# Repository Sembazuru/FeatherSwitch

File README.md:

# FeatherSwitch
AdaFruit Feather Enable Switch Board. Designed in <a href="http://kicad-pcb.org/">KiCAD.</a>

This board connects the GND pin and the EN pin (opposite sides of the Feather boards) together with a switch,
ideally across the underside of the Feather board. The switch is next to the battery connector.
It doesn't obscure the battery connector, but does make it more difficult to remove the battery.
This can be ameliorated by mounting this board to either a Feather Wing, or the Feather Doubler (or Tripler)
This allows conveniently turning off the board without disconnecting either a battery or the USB cable.
This first version of the board has hole size and spacing for AdaFruit#<a href="https://www.adafruit.com/product/805">805</a> slide switch or mechanical equivalent.
Note: The holes are slightly too small for 0.25"sq header pins.

The design works best if the 2oz copper option is selected to get 0.8mm (1/32", or half standard) thick boards. These boards are available to order using the button below.</br>
<a href="https://oshpark.com/shared_projects/68Dy2ual"></img></a>

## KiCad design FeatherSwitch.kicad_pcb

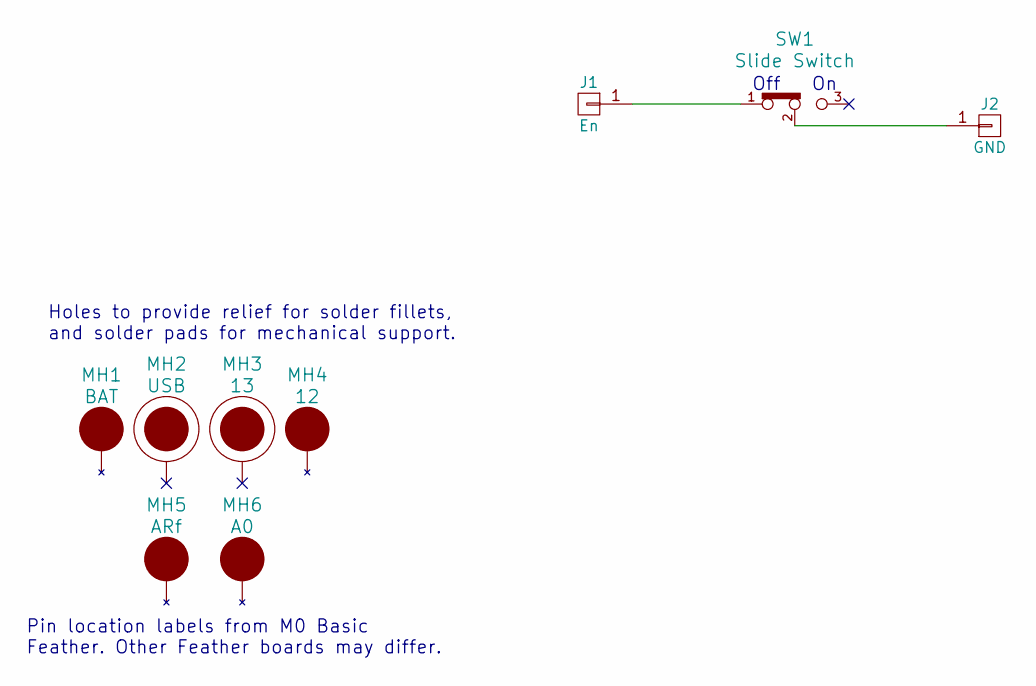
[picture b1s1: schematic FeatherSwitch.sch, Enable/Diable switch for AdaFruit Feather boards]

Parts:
J1: En; PAD_AdaFruit_Feather
J2: GND; PAD_AdaFruit_Feather
MH1: BAT; PAD-Clear_AdaFruit_Feather
MH2: USB; PAD_AdaFruit_Feather
MH3: 13; PAD_AdaFruit_Feather
MH4: 12; PAD-Clear_AdaFruit_Feather
MH5: ARf; PAD-Clear_AdaFruit_Feather
MH6: A0; PAD-Clear_AdaFruit_Feather
SW1: Slide Switch; SW_ADAFRUIT_508

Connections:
unnamed: J1.1, SW1.1 (Pole1)
unnamed: J2.1, SW1.2 (Throw)

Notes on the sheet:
Off
Pin location labels from M0 Basic Feather. Other Feather boards may differ.
Holes to provide relief for solder fillets, and solder pads for mechanical support.

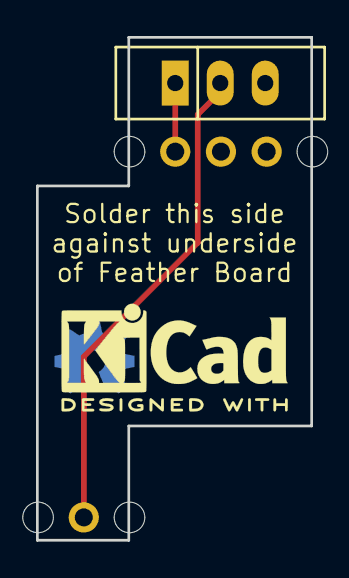
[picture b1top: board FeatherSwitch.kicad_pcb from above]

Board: 2 copper layers, 15.2 x 27.9 mm, 9 parts (0 on the bottom side), 2 nets.

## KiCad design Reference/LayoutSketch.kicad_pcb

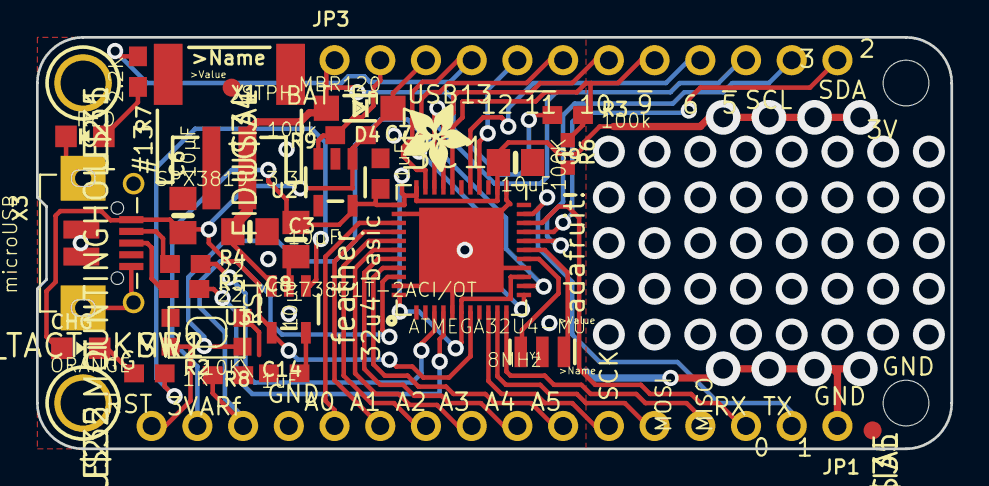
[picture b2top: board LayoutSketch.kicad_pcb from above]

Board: 2 copper layers, 50.8 x 22.9 mm, 36 parts (0 on the bottom side), 37 nets.

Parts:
@HOLE0, @HOLE1: (no value)
C3, C6, C8: 10µF; 0805-NO
C7, C14: 1uF; 0603-NO
C9: 10uF; 0805-NO
CHG: ORANGE; CHIPLED_0805_NOOUTLINE
D4: MBR120; SOD-123
IC1: ATMEGA32U4-MU; TQFN44_7MM
JP1: 1X16_ROUND
JP3: 1X12_ROUND
L: RED; CHIPLED_0805_NOOUTLINE
R2: 1K; 0603-NO
R3, R9: 100k; 0603-NO
R4, R5: 22; 0603-NO
R6: 100K; _0603MP
R7: 2.2K; 0603-NO
R8: 10K\; 0603-NO
SW1: SPST_TACT-KMR2; KMR2
U2: SPX3819-3.3; SOT23-5
U3: MCP73831T-2ACI/OT; SOT23-5
U$4: ADAFRUIT_5MM
U$5: FEATHERLOGO
U$6: PCBFEAT-REV-040
U$7: ADAFRUIT_3.5MM
U$31, U$32: MOUNTINGHOLE2.5; MOUNTINGHOLE_2.5_PLATED
U$34, U$35: FIDUCIAL; FIDUCIAL_1MM
X1: JSTPH; JSTPH2
X3: microUSB; 4UCONN_20329_V2
Y1: 8MHz; RESONATOR-SMD

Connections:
0: IC1.20, JP1.3
1: IC1.21, JP1.2
2: IC1.19, JP3.12
3: IC1.18, JP3.11
5: IC1.31, JP3.10
6: IC1.27, JP3.9
9: IC1.29, JP3.8, R3.2, R6.1
10: IC1.30, JP3.7
11: IC1.12, JP3.6
12: IC1.26, JP3.5
13: IC1.32, JP3.4, R7.1
+3V3: C7.1, C8.1, C9.1, IC1.6, IC1.14, IC1.24, IC1.33, IC1.34, IC1.44, JP1.15, U2.5
A0: IC1.36, JP1.12
A1: IC1.37, JP1.11
A2: IC1.38, JP1.10
A3: IC1.39, JP1.9
A4: IC1.40, JP1.8
A5: IC1.41, JP1.7
AREF: C14.1, IC1.42, JP1.14
D+: IC1.4, R5.2
D-: IC1.3, R4.2
EN: JP3.2, R9.2, U2.3
GND: C3.2, C6.2, C7.2, C8.2, C9.2, C14.2, IC1.5, IC1.15, IC1.23, IC1.35, IC1.43, JP1.1, JP1.13, L.C, R6.2, R8.2, SW1.2, SW1.4, U2.2, U3.2, X1.1, X3.GND, Y1.2
MISO: IC1.11, JP1.4
MOSI: IC1.10, JP1.5
unnamed: CHG.C, R2.1
unnamed: L.A, R7.2
unnamed: R2.2, U3.1
unnamed: R8.1, U3.5
unnamed: IC1.16, Y1.3
unnamed: IC1.17, Y1.1
unnamed: R5.1, X3.D+
unnamed: R4.1, X3.D-
RST: IC1.13, JP1.16, SW1.1, SW1.3
SCK: IC1.9, JP1.6
VBAT: C3.1, D4.A, JP3.1, R3.1, U3.3, X1.2
VBUS: C6.1, CHG.A, D4.C, IC1.7, JP3.3, R9.1, U2.1, U3.4, X3.VBUS

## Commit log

2017-04-16 :boom::camel: Added .gitattributes & .gitignore files
2017-04-16 First commit to GitHub
    This is the state for the first boards. The switch is specifically
    designed for the AdaFruit part number 508 slide switch.
2017-04-16 Archive filename corrected
    Corrected archive filename from:
    FeatherSwitch_sch1.1.0_pcb1.1.0
    to:
    FeatherSwitch_sch1.0.0_pcb1.0.0
2017-04-22 Add Photos
    Add Photos to use in Wiki
2017-04-25 Add annotated images
2017-12-03 V1.0.0 Gerbers
    Generate Gerbers (First production run was done with KiCAD file at
    OSHPark.)
